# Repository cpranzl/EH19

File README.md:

# EH19
KiCAD Tutorial from Easterhegg 2019

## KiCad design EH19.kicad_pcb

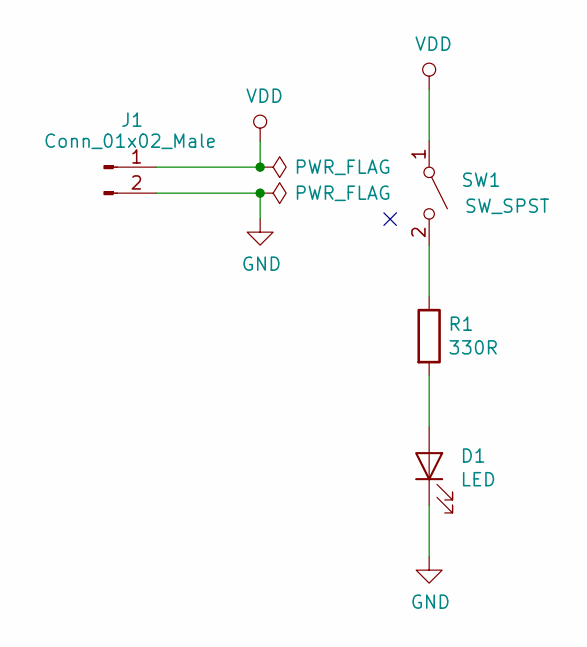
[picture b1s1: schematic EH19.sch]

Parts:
D1: LED; LED_D5.0mm
J1: Conn_01x02_Male; PhoenixContact_GMSTBA_2,5_2-G_1x02_P7.50mm_Horizontal
R1: 330R; R_Axial_DIN0516_L15.5mm_D5.0mm_P20.32mm_Horizontal
SW1: SW_SPST; SW_PUSH_6mm_H5mm

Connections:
GND: D1.1 (K), J1.2
unnamed: D1.2 (A), R1.2
unnamed: R1.1, SW1.2 (B)
VDD: J1.1, SW1.1 (A)

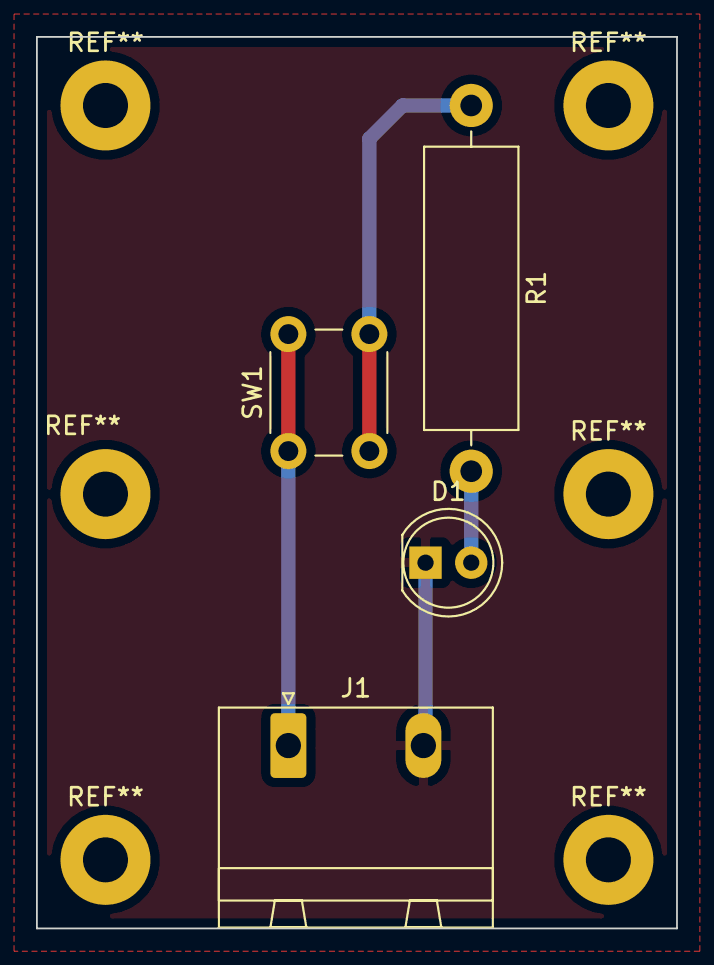
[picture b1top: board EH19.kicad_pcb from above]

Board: 2 copper layers, 35.6 x 49.5 mm, 4 parts (0 on the bottom side), 4 nets.
